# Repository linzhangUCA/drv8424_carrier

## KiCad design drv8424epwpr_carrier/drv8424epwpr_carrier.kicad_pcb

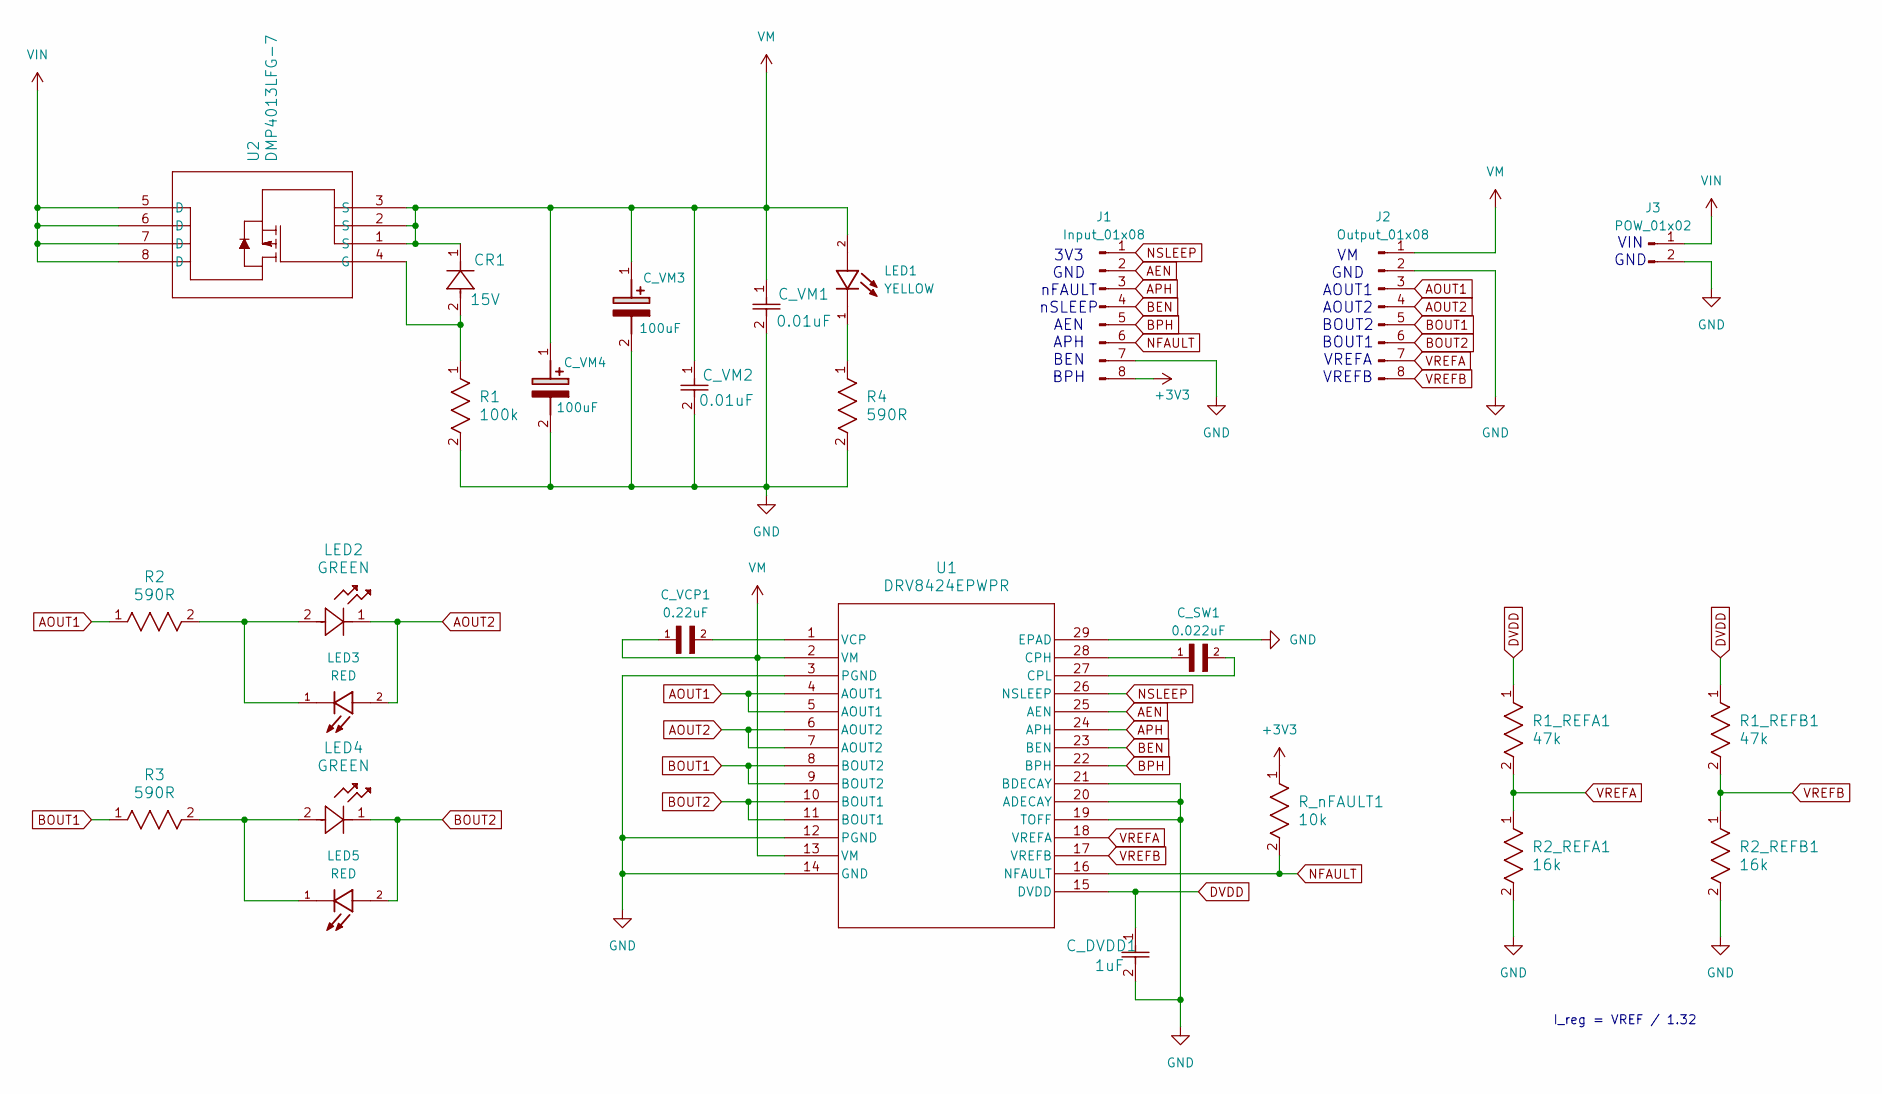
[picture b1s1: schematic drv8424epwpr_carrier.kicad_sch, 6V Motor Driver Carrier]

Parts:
CR1: 15V; SOD123_DIO
C_DVDD1: 1uF; C_0805_2012Metric
C_SW1: 0.022uF; C_0805_2012Metric
C_VCP1: 0.22uF; C_0805_2012Metric
C_VM1, C_VM2: 0.01uF; C_0805_2012Metric
C_VM3, C_VM4: 100uF; EEE0GA101SR; Mouser Part Number 667-EEE-1AA101WR
J1: Input_01x08; PinHeader_1x08_P2.54mm_Vertical
J2: Output_01x08; PinHeader_1x08_P2.54mm_Vertical
J3: POW_01x02; PinHeader_1x02_P2.54mm_Horizontal
LED1: YELLOW; LED_0805_2012Metric; PARTREV V.10A
LED2, LED4: GREEN; LED_0805_2012Metric
LED3, LED5: RED; LED_0805_2012Metric; PARTREV V.10A
R1: 100k; R_1206_3216Metric
R1_REFA1, R1_REFB1: 47k; R_1206_3216Metric
R2, R3, R4: 590R; R_1206_3216Metric
R2_REFA1, R2_REFB1: 16k; R_1206_3216Metric
R_nFAULT1: 10k; R_1206_3216Metric
U1: DRV8424EPWPR; HTSSOP28_PWP_TEX-M
U2: DMP4013LFG-7; SON8_DMP4013LFG-7_DIO

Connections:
+3V3: J1.8, R_nFAULT1.1
AEN: J1.2, U1.25 (AEN)
AOUT1: J2.3, R2.1, U1.4 (AOUT1), U1.5 (AOUT1)
AOUT2: J2.4, LED2.1, LED3.2, U1.6 (AOUT2), U1.7 (AOUT2)
APH: J1.3, U1.24 (APH)
BEN: J1.4, U1.23 (BEN)
BOUT1: J2.5, R3.1, U1.8 (BOUT2), U1.9 (BOUT2)
BOUT2: J2.6, LED4.1, LED5.2, U1.10 (BOUT1), U1.11 (BOUT1)
BPH: J1.5, U1.22 (BPH)
DVDD: C_DVDD1.1, R1_REFA1.1, R1_REFB1.1, U1.15 (DVDD); also elsewhere on the board
GND: C_DVDD1.2, C_VM1.2, C_VM2.2, C_VM3.2 (-), C_VM4.2 (-), J1.7, J2.2, J3.2, R1.2, R2_REFA1.2, R2_REFB1.2, R4.2, U1.3 (PGND), U1.12 (PGND), U1.14 (GND), U1.19 (TOFF), U1.20 (ADECAY), U1.21 (BDECAY), U1.29 (EPAD); also elsewhere on the board
NFAULT: J1.6, R_nFAULT1.2, U1.16 (NFAULT)
NSLEEP: J1.1, U1.26 (NSLEEP)
unnamed: LED1.1, R4.1
unnamed: LED2.2, LED3.1, R2.2
unnamed: LED4.2, LED5.1, R3.2
unnamed: C_SW1.1, U1.28 (CPH)
unnamed: C_SW1.2, U1.27 (CPL)
unnamed: C_VCP1.2, U1.1 (VCP)
unnamed: CR1.2, R1.1, U2.4 (G)
VIN: J3.1, U2.5 (D), U2.6 (D), U2.7 (D), U2.8 (D)
VM: CR1.1, C_VCP1.1, C_VM1.1, C_VM2.1, C_VM3.1 (+), C_VM4.1 (+), J2.1, LED1.2, U1.2 (VM), U1.13 (VM), U2.1 (S), U2.2 (S), U2.3 (S)
VREFA: J2.7, R1_REFA1.2, R2_REFA1.1, U1.18 (VREFA)
VREFB: J2.8, R1_REFB1.2, R2_REFB1.1, U1.17 (VREFB)

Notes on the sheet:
VIN GND
I_reg = VREF / 1.32
3V3 GND nFAULT nSLEEP AEN APH BEN BPH
VM GND AOUT1 AOUT2 BOUT2 BOUT1 VREFA VREFB

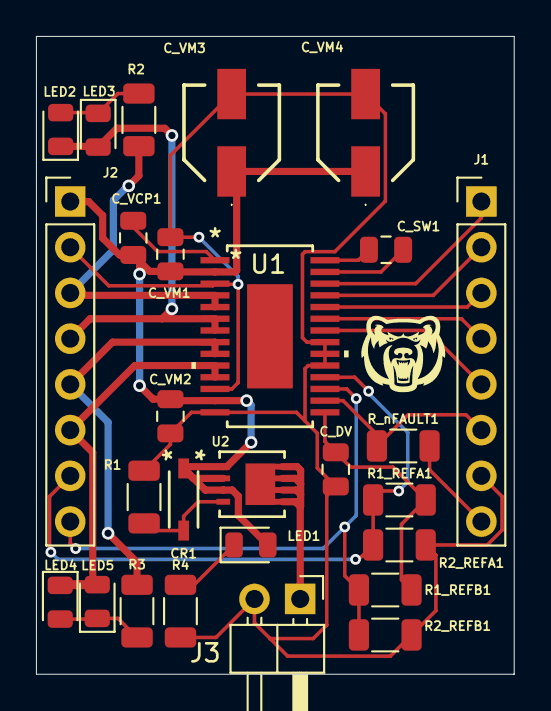
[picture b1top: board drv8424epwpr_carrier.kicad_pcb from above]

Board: 2 copper layers, 26.5 x 35.4 mm, 27 parts (0 on the bottom side), 24 nets.

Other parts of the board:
C_DV: 1uF; C_0805_2012Metric

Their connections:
DVDD: C_DV.1; also elsewhere on the board
GND: C_DV.2; also elsewhere on the board

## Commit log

2025-02-11 start project
2025-02-11 add reverse protection circuit
2025-02-11 update schematic
2025-02-12 update current regulation circuit
2025-02-12 finish schematic
2025-02-12 add motor dir indication LEDs
2025-02-12 add power indication LED
2025-02-13 add footprint
2025-02-13 update pin headers
2025-02-13 get ready for PCB
2025-02-14 update layout
2025-02-15 start routing
2025-02-15 update model lib
2025-02-15 update pcb
2025-02-16 update routing
2025-02-16 update J2 arrange
2025-02-16 update drv8424 footprint, but issue not fixed
